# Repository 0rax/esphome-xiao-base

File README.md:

# XIAO Base for ESPHome

The XIAO Base for ESPHome is a custom PCB designed to be used with the [ESPHome](https://esphome.io/) firmware as a base for creating new sensors.

It was made as a carrier board for the XIAO series of microcontrollers with an OLED display and three switches while providing an easy-to-access header on the back for standard communication protocols (I²C, UART and SPI).

A cutout has also been left for the underside of the XIAO to allow access to the battery pads available on the underside of some modules (such as the [XIAO ESP32C6]).

## PCB

|           Render            |           Front           |          Back           |
| :-------------------------: | :-----------------------: | :---------------------: |
| [![PCB Render]][PCB Render] | [![PCB Front]][PCB Front] | [![PCB Back]][PCB Back] |

[PCB Render]: assets/pcb-render.png
[PCB Front]: output/pcb/img/pcb-top.png
[PCB Back]: output/pcb/img/pcb-bottom.png

The PCB has been designed in [KiCad EDA 9.0](https://www.kicad.org/).

You can preview the project files using [KiCanvas](https://kicanvas.org/?github=https%3A%2F%2Fgithub.com%2F0rax%2Fesphome-xiao-base%2Ftree%2Fmain%2Fpcb) directly in your browser, the exported schematic is also available under [`output/schematics`](output/schematics/).

### PCB Order

The necessary Gerber files to order the PCB are available in the [`output/fabrication/jlcpcb`](output/fabrication/jlcpcb) directory. They have been generated specifically for [JLCPCB](https://jlcpcb.com/) using [KiBot](https://kibot.readthedocs.io/). They should be compatible with other PCB manufacturers too.

Here is the list of parameters to use for the PCB order:

| Parameters                           | Value                  | Parameters                     | Value                        |
| ------------------------------------ | ---------------------- | ------------------------------ | ---------------------------- |
| **Base Material**                    | FR4                    | **Copper Weight**              | 1 oz                         |
| **Layers**                           | 2                      | **Via Covering**               | Tented                       |
| **Dimensions**                       | 40 × 30 mm             | **Min Via Hole Size**          | 0.3 mm                       |
| **PCB Thickness**                    | 1.2 or 1.6 mm          | **Board Outline Tolerance**    | ± 0.2 mm                     |
| **PCB Color** [^pcb-color]           | Black                  | **Mark on PCB** [^jlcpcb-mark] | 2D Barcode (Serial Number)   |
| **Silkscreen**                       | White                  |                                | > Printing: Number Only      |
| **Surface Finish** [^surface-finish] | Lead Free HASL or ENIG |                                | > Position: Specify Position |

[^pcb-color]: You can select any PCB color you want but some manufacturers such as JLCPCB may charge you more for uncommon combos (such as Blue PCB + ENIG Surface Finish).
[^surface-finish]: The "HASL (with lead)" option is extremely discouraged due to the risk of lead poisoning. We strongly recommend paying the premium for the "Lead Free HASL" option.
[^jlcpcb-mark]: JLCPCB specific option, a pre-configured footprint has been added for a serial number to be printed on the back of the PCB.

### BOM

| Part            | Ref.                                                         | Quantity | Remarks                                                                                                                                       |
| --------------- | ------------------------------------------------------------ | :------: | --------------------------------------------------------------------------------------------------------------------------------------------- |
| PCB             | [XIAO Base for ESPHome PCB](./README.md#pcb)                 |    1     | See the previous section on how to order it.                                                                                                  |
| XIAO Controller | [XIAO ESP32C3], [XIAO ESP32C6] or [XIAO ESP32S3]             |    1     | Any ESPHome compatible XIAO controller should work.                                                                                           |
| Tactile Switch  | [SCHURTER 1301.9303]                                         |    3     | Any 6 × 6 mm thru-hole tactile switch should work. We recommend a model with a stem length of 3 mm or more.                                   |
| OLED Display    | [SSD1306 0.91" OLED Display] or [SSD1107 0.96" OLED Display] |    1     | Any SSD1306 or SSD1106 I²C based display should work. The PCB was designed to accommodate both 0.91" (128 × 32) and 0.96" (64 × 128) modules. |

[SSD1306 0.91" OLED Display]: https://www.aliexpress.com/item/32777216785.html
[SSD1107 0.96" OLED Display]: https://aliexpress.com/item/1005005814186982.html
[XIAO ESP32C3]: https://www.seeedstudio.com/Seeed-XIAO-ESP32C3-p-5431.html
[XIAO ESP32C6]: https://www.seeedstudio.com/Seeed-Studio-XIAO-ESP32C6-p-5884.html
[XIAO ESP32S3]: https://www.seeedstudio.com/XIAO-ESP32S3-p-5627.html
[SCHURTER 1301.9303]: https://www.digikey.com/en/products/detail/schurter-inc/1301-9303/3189753

## ESPHome

Example ESPHome configuration files can be found in the [`esphome`](esphome/) directory.

Two are provided for the [XIAO ESP32C6] and [XIAO ESP32S3] with two different type of OLED display.
They should be easily modifiable to fit any ESPHome compatible XIAO microcontrollers and displays.

## Add-ons

### AQStation

|                 Front                 |                Back                 |
| :-----------------------------------: | :---------------------------------: |
| [![AQStation Front]][AQStation Front] | [![AQStation Back]][AQStation Back] |

[AQStation Front]: output/addons/aqstation/img/aqstation-top.png
[AQStation Back]: output/addons/aqstation/img/aqstation-bottom.png

An indoor air quality station fit to accept a [Plantower PMSA003](https://plantower.com/en/products_33/77.html) particulate matter sensor and a [Bosch BME688](https://www.bosch-sensortec.com/products/environmental-sensors/gas-sensors/bme688/) gas, temperature, humidity and pressure sensor.

In order to support as many breakouts as possible, the PCB was designed to be modular with 3 different headers. Here is a list of what should be compatible with the PCB:

- Adafruit BME680 Header
  - [Adafruit BME280](https://www.adafruit.com/product/2652)
  - [Adafruit BME680](https://www.adafruit.com/product/3660)
  - [Adafruit BME688](https://www.adafruit.com/product/5046)
- Adafruit I2C Header
  - [BME680 Purple Breakout](https://www.studiopieters.nl/bme680-gas-sensor/)
  - A lot of other sensor breakouts share compatible pinouts that are not from the BME680 family such as:
    - [Adafruit Si7021](https://www.adafruit.com/product/3251)
    - [Adafruit MCP9808](https://www.adafruit.com/product/1782)
    - [Adafruit AHT20](https://www.adafruit.com/product/4566)
    - [DFRobot Fermion SHT40](https://www.dfrobot.com/product-2437.html)
    - [DFRobot Fermion SHT31](https://www.dfrobot.com/product-2013.html)
    - [DFRobot Fermion SHTC3](https://www.dfrobot.com/product-2436.html)
    - [DFRobot Fermion AHT20](https://www.dfrobot.com/product-2603.html)
    - [DFRobot Fermion SHT35](https://www.dfrobot.com/product-2016.html)
- DFRobot BME680 Header
  - [DFRobot Fermion BME680](https://www.dfrobot.com/product-2143.html)
  - [DFRobot Fermion BME688](https://www.dfrobot.com/product-2918.html)

The PCB also includes a STEMMA QT / Qwiic connector to further expand the capabilities of the device, this header is compatible with the following ecosystems:

- [Adafruit STEMMA QT](https://learn.adafruit.com/introducing-adafruit-stemma-qt/what-is-stemma-qt)
- [SparkFun Qwiic](https://www.sparkfun.com/qwiic)
- [Soldered easyC](https://soldered.com/easyC/)

### SensorBoard

|                   Front                   |                  Back                   |
| :---------------------------------------: | :-------------------------------------: |
| [![SensorBoard Front]][SensorBoard Front] | [![SensorBoard Back]][SensorBoard Back] |

[SensorBoard Front]: output/addons/sensorboard/img/sensorboard-top.png
[SensorBoard Back]: output/addons/sensorboard/img/sensorboard-bottom.png

A development board to test and develop ESPHome configurations using various breakout boards and sensors.

It was designed to accept up to 3 sensors on the board using different headers and has 2 STEMMA QT / Qwiic connectors to expand it even further. This board can either be used as an add-on for the XIAO Base or as a standalone board by plugging a XIAO MCU directly.

The different headers / connectors are:

- Sensor 1
  - Adafruit I2C Header
  - SparkFun I2C Header
  - Pimoroni I2C Garden
- Sensor 2
  - Adafruit I2C Header
  - SparkFun I2C Header
  - Pimoroni I2C Garden
- Sensor 3
  - Adafruit I2C Header
  - Adafruit BME680 Header
  - RGB LED header
- 2× STEMMA QT / Qwiic connectors

Make sure to check out the pinouts and notes on the PCB for more information on which pins are used for what as well as the back of the PCB for more information on header compatibility.
A more complete compatibility list can be found in the schematic files.

## Notes

### Potential Modifications

- The XIAO microcontroller is currently soldered at the front of the PCB making the OLED display require a double stacked header for clearance as well as force the use of switches with extended stem. Moving it to the back of the PCB would allow for everything in the front to be made smaller but would make access to the battery pads on the back of the XIAO and the `RST` / `BOOTSEL` buttons more difficult.
- Adding some sort of STEMMA QT / Qwiic connector to the back of the PCB would make it easier to integration some sensors though space is quite limited.

## License

This design is licensed under the [CERN Open Hardware Licence Version 2 – Strongly Reciprocal (CERN-OHL-S-2.0)](https://opensource.org/license/cern-ohl-s).

You are free to use, modify, and distribute this design for any purpose, provided that:

- **Attribution**: Appropriate credit is given, a link to the license is provided, and any modifications are clearly indicated.
- **Reciprocity**: Any derivative works must be released under the same license.

If you are a retailer or business interested in producing or selling this design or related products, I’d love to discuss it! Please feel free to reach out, so we can explore potential arrangements.

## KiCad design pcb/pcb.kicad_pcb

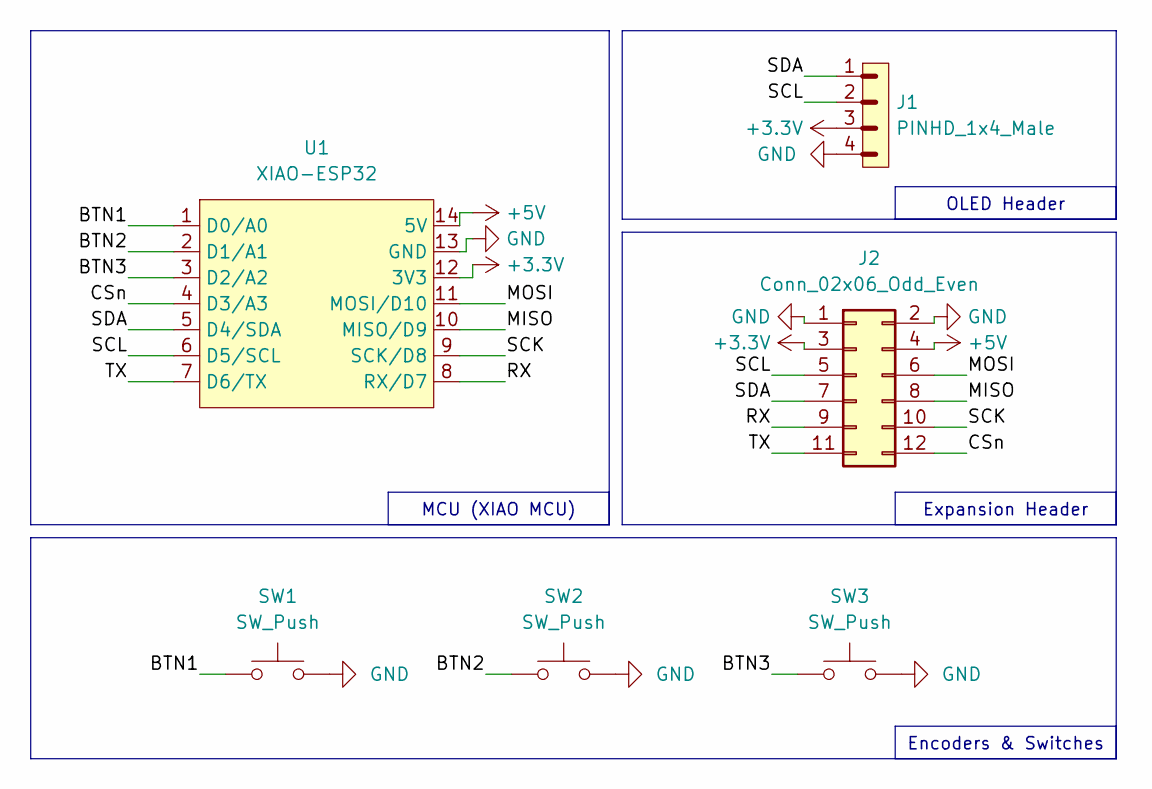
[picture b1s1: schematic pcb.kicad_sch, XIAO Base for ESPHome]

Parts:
J1: PINHD_1x4_Male; OLED_SSD1306_128x32_0.91inch_I2C
J2: Conn_02x06_Odd_Even; PinHeader_2x06_P2.54mm_Vertical
SW1, SW2, SW3: SW_Push; SW_PUSH_6mm
U1: XIAO-ESP32; MCU_XIAO-RP2040

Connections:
+3.3V: J1.3, J2.3, U1.12 (3V3)
+5V: J2.4, U1.14 (5V)
/BTN1: SW1.1, U1.1 (D0/A0)
/BTN2: SW2.1, U1.2 (D1/A1)
/BTN3: SW3.1, U1.3 (D2/A2)
/CSn: J2.12, U1.4 (D3/A3)
/MISO: J2.8, U1.10 (MISO/D9)
/MOSI: J2.6, U1.11 (MOSI/D10)
/RX: J2.9, U1.8 (RX/D7)
/SCK: J2.10, U1.9 (SCK/D8)
/SCL: J1.2, J2.5, U1.6 (D5/SCL)
/SDA: J1.1, J2.7, U1.5 (D4/SDA)
/TX: J2.11, U1.7 (D6/TX)
GND: J1.4, J2.1, J2.2, SW1.2, SW2.2, SW3.2, U1.13 (GND)

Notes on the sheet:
Expansion Header
MCU (XIAO MCU)
OLED Header
Encoders & Switches

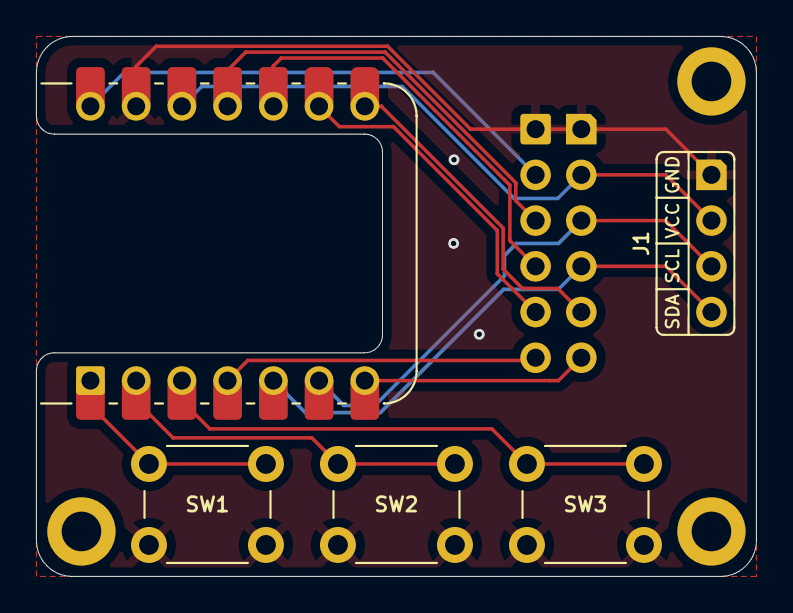
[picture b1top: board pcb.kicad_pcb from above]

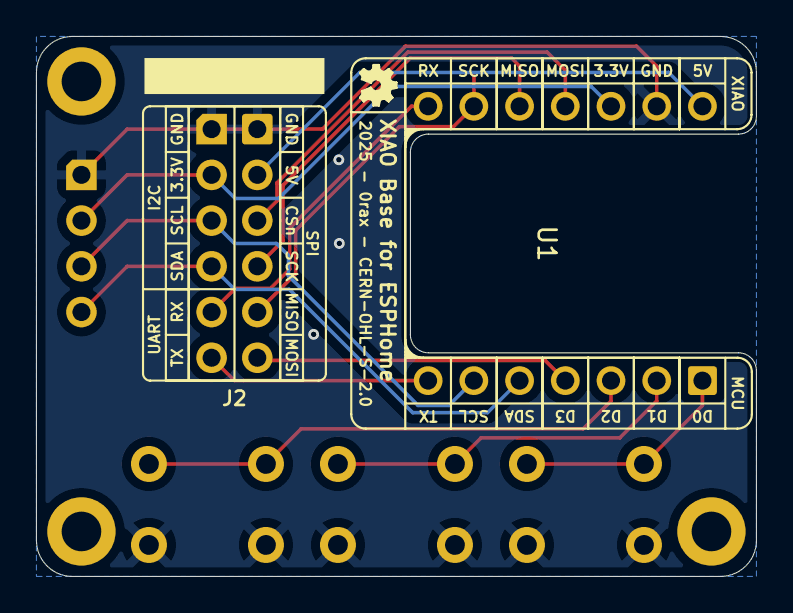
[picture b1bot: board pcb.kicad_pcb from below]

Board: 2 copper layers, 40.0 x 30.0 mm, 10 parts (2 on the bottom side), 14 nets.

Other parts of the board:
H1, H2, H3: MountingHole_2.2mm_M2_ISO14580_Pad
REF1: JLCPCB_SerialNumber_2x10mm

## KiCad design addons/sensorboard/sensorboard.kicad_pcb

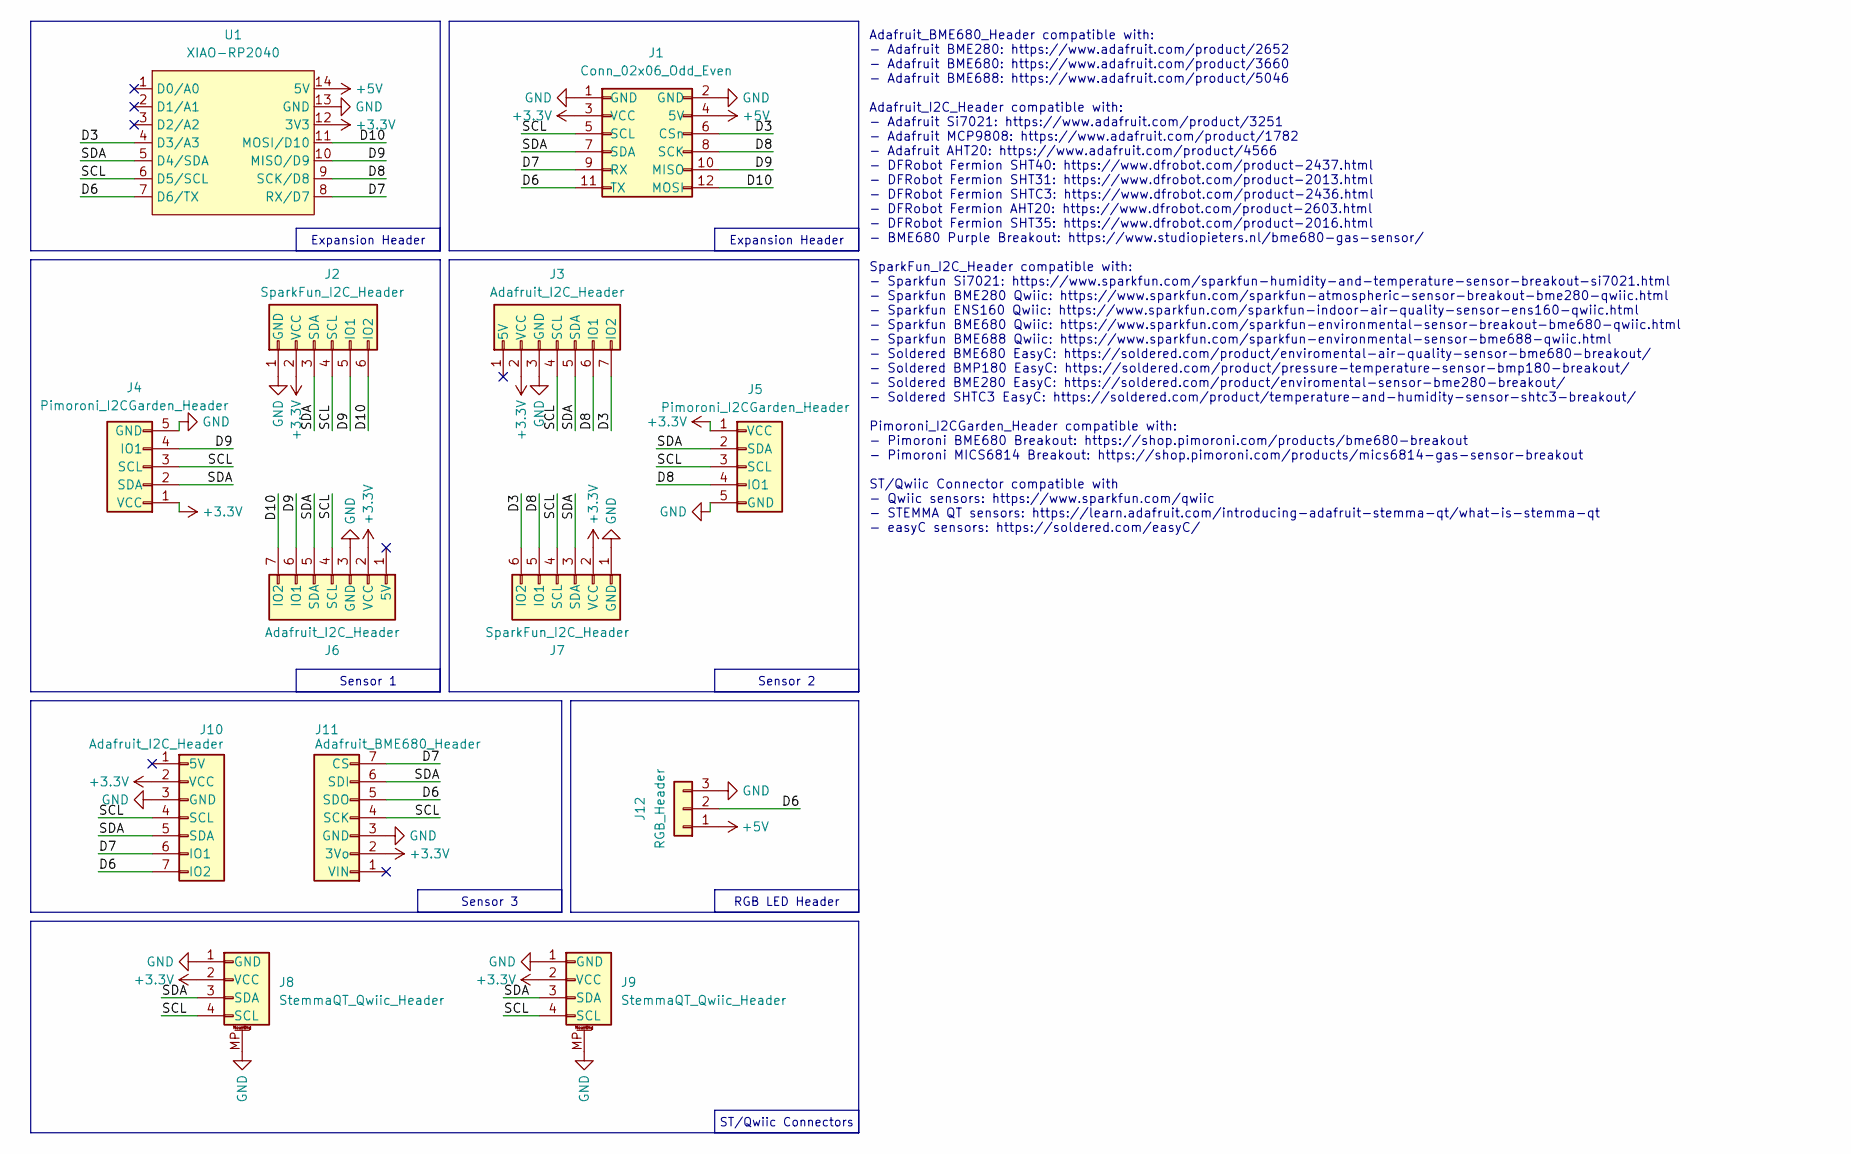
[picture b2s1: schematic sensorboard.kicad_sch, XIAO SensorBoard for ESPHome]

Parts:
J1: Conn_02x06_Odd_Even; XIAOBase_Header
J2, J7: SparkFun_I2C_Header
J3, J6, J10: Adafruit_I2C_Header
J4, J5: Pimoroni_I2CGarden_Header
J8, J9: StemmaQT_Qwiic_Header; JST_SH_SM04B-SRSS-TB_1x04-1MP_P1.00mm_Horizontal
J11: Adafruit_BME680_Header
J12: RGB_Header; NeoPixel_Header
U1: XIAO-RP2040; MCU_XIAO-RP2040

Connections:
+3.3V: J1.3 (VCC), J2.2 (VCC), J3.2 (VCC), J4.1 (VCC), J5.1 (VCC), J6.2 (VCC), J7.2 (VCC), J8.2 (VCC), J9.2 (VCC), J10.2 (VCC), J11.2 (3Vo), U1.12 (3V3)
+5V: J1.4 (5V), J12.1, U1.14 (5V)
/D3: J1.6 (CSn), J3.7 (IO2), J7.6 (IO2), U1.4 (D3/A3)
/D6: J1.11 (TX), J10.7 (IO2), J11.5 (SDO), J12.2, U1.7 (D6/TX)
/D7: J1.9 (RX), J10.6 (IO1), J11.7 (CS), U1.8 (RX/D7)
/D8: J1.8 (SCK), J3.6 (IO1), J5.4 (IO1), J7.5 (IO1), U1.9 (SCK/D8)
/D9: J1.10 (MISO), J2.5 (IO1), J4.4 (IO1), J6.6 (IO1), U1.10 (MISO/D9)
/D10: J1.12 (MOSI), J2.6 (IO2), J6.7 (IO2), U1.11 (MOSI/D10)
/SCL: J1.5 (SCL), J2.4 (SCL), J3.4 (SCL), J4.3 (SCL), J5.3 (SCL), J6.4 (SCL), J7.4 (SCL), J8.4 (SCL), J9.4 (SCL), J10.4 (SCL), J11.4 (SCK), U1.6 (D5/SCL)
/SDA: J1.7 (SDA), J2.3 (SDA), J3.5 (SDA), J4.2 (SDA), J5.2 (SDA), J6.5 (SDA), J7.3 (SDA), J8.3 (SDA), J9.3 (SDA), J10.5 (SDA), J11.6 (SDI), U1.5 (D4/SDA)
GND: J1.1 (GND), J1.2 (GND), J2.1 (GND), J3.3 (GND), J4.5 (GND), J5.5 (GND), J6.3 (GND), J7.1 (GND), J8.1 (GND), J8.MP (MountPin), J9.1 (GND), J9.MP (MountPin), J10.3 (GND), J11.3 (GND), J12.3, U1.13 (GND)

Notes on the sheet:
Expansion Header
RGB LED Header
Sensor 1
ST/Qwiic Connectors
Adafruit_BME680_Header compatible with: - Adafruit BME280: https://www.adafruit.com/product/2652 - Adafruit BME680: https://www.adafruit.com/product/3660 - Adafruit BME688: https://www.adafruit.com/product/5046 Adafruit_I2C_Header compatible with: - Adafruit Si7021: https://www.adafruit.com/product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
Sensor 3
Sensor 2

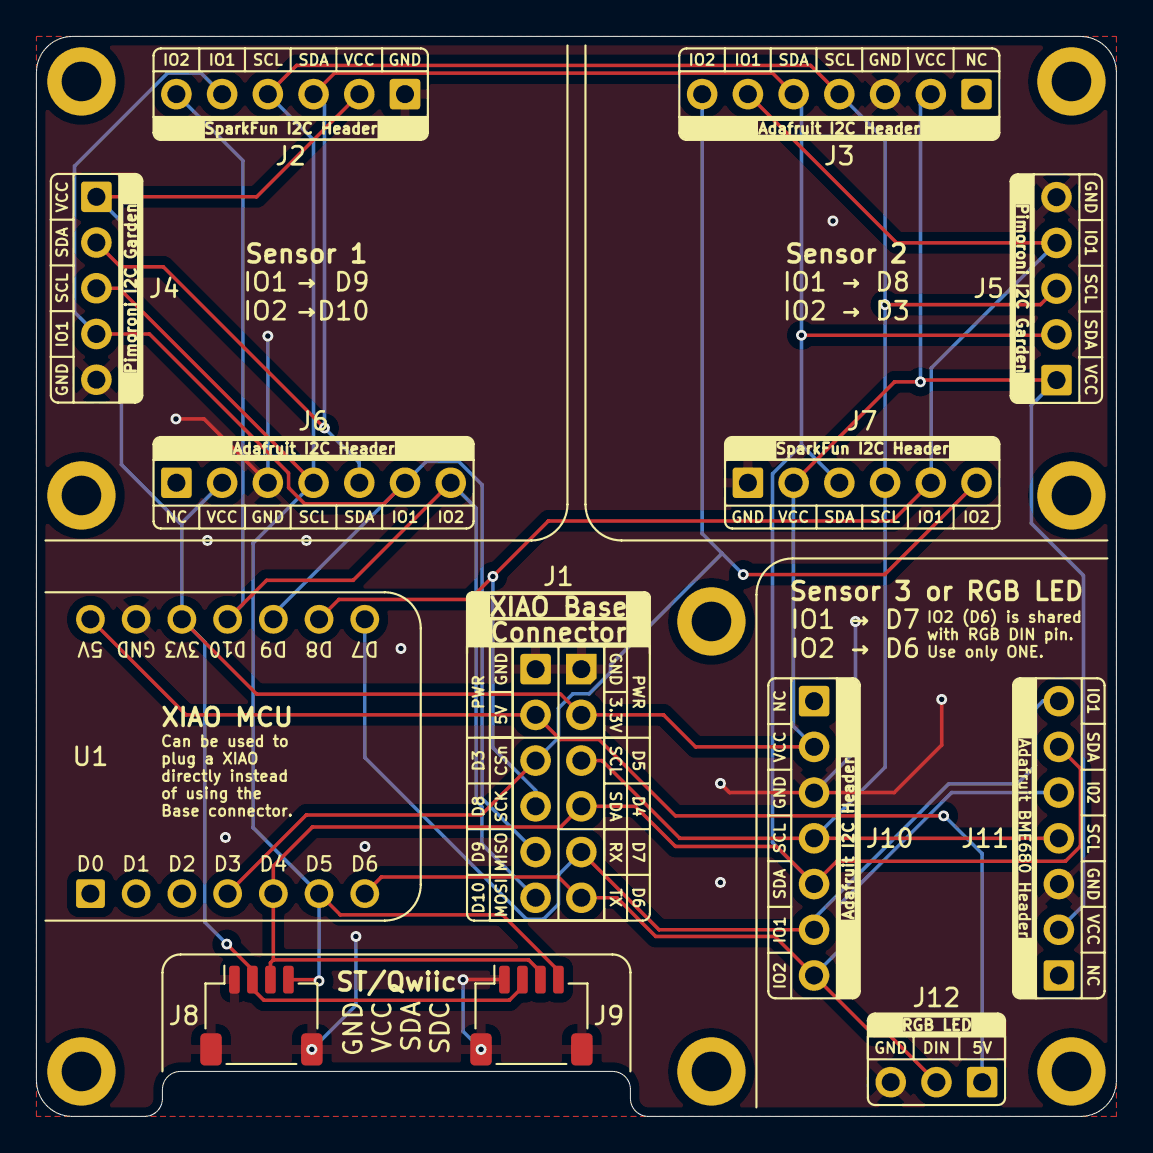
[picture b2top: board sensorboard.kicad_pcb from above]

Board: 2 copper layers, 60.0 x 60.0 mm, 21 parts (0 on the bottom side), 11 nets.

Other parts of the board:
H1, H3, H4, H5, H7, H8, H9, H10: MountingHole_2.2mm_M2_ISO14580_Pad

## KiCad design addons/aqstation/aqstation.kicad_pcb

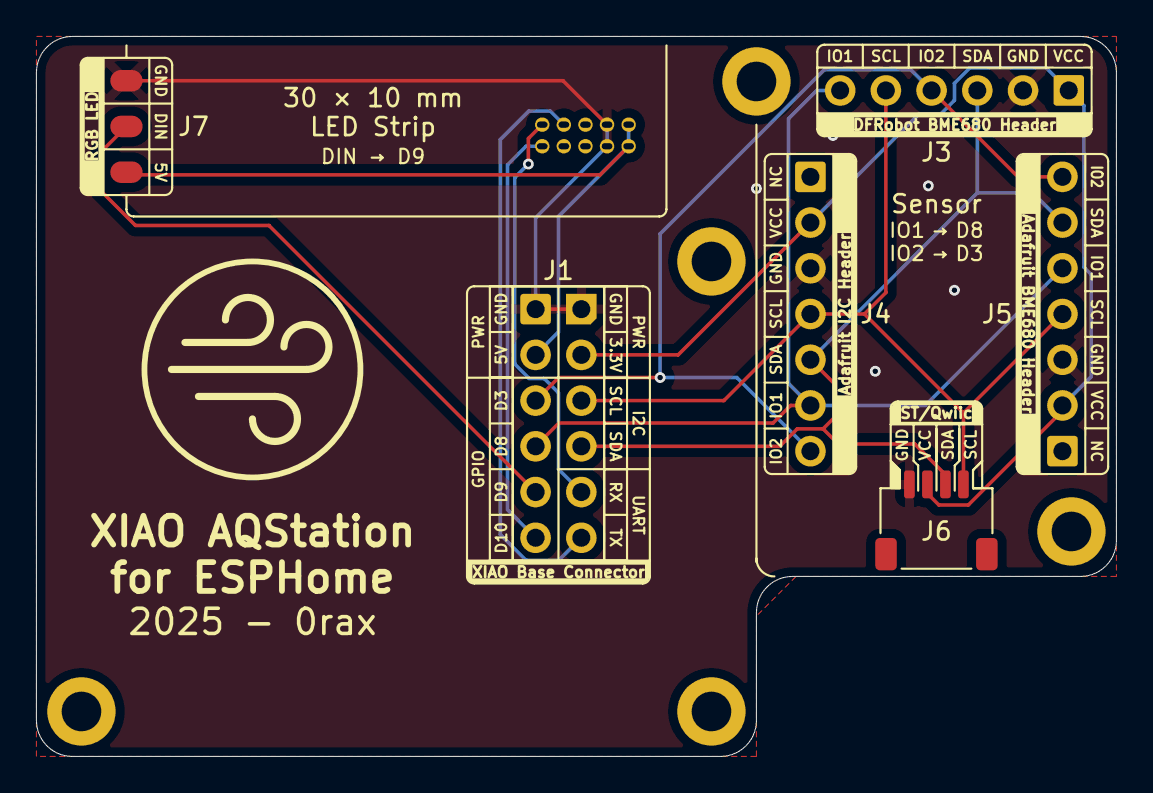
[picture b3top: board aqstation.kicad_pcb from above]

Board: 2 copper layers, 60.0 x 40.0 mm, 12 parts (1 on the bottom side), 11 nets.

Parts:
H1, H3, H4, H5, H6: MountingHole_2.2mm_M2_ISO14580_Pad
J1: Conn_02x06_Odd_Even; XIAOBase_Header
J2: PMSA003
J3: DFRobot_BME680_Header
J4: Adafruit_I2C_Header
J5: Adafruit_BME680_Header
J6: StemmaQT_Qwiic_Header; JST_SH_SM04B-SRSS-TB_1x04-1MP_P1.00mm_Horizontal
J7: RGB_Header; NeoPixel_Header

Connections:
+3.3V: J1.3 (VCC), J3.1 (VCC), J4.2 (VCC), J5.2 (3Vo), J6.2 (VCC)
+5V: J1.4 (5V), J2.1 (VCC), J2.2 (VCC), J7.1
/ADDR: J1.8 (D8), J3.6 (MI), J4.6 (IO1), J5.5 (SDO)
/EN: J1.6 (D3), J3.4 (CS), J4.7 (IO2), J5.7 (CS)
/LEDIO: J1.10 (D9), J7.2
/RX: J1.9 (RX), J2.9 (TXD)
/SCL: J1.5 (SCL), J3.5 (SCK), J4.4 (SCL), J5.4 (SCK), J6.4 (SCL)
/SDA: J1.7 (SDA), J3.3 (MO), J4.5 (SDA), J5.6 (SDI), J6.3 (SDA)
/SET: J1.12 (D10), J2.10 (SET)
/TX: J1.11 (TX), J2.7 (RXD)
GND: J1.1 (GND), J1.2 (GND), J2.3 (GND), J2.4 (GND), J3.2 (GND), J4.3 (GND), J5.3 (GND), J6.1 (GND), J7.3

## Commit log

2025-03-26 Initial PCB design
2025-04-09 Add example ESPHome configurations
2025-04-09 Add PCB render
2025-04-09 Update Schematics and PCB properties
2025-04-09 Add release badge to README.md
2025-04-27 Add AQStation & SensorBoard addons
2025-04-29 More compact version of the AQStation
2025-04-29 Switch LED header to just some pads
2025-04-29 Remove solderpaste from pcbdraw export
2025-04-29 Cleanup wiring
2025-05-05 Finalize aqstation
2025-05-19 Fix issues with the initial version and add support for DFRobot BME breakouts
    Update documentation

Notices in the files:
README.md:
License: CERN-OHL-S-2.0
pcb/pcb.kicad_pcb:
2025 - 0rax - CERN-OHL-S-2.0
